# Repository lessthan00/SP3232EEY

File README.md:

# SP3232EEY

[SP3232EEY](https://www.jlc-smt.com/lcsc/detail?componentCode=C13482)

RS232芯片

[参考](https://oshwhub.com/jixin/TTL_RS232_SP3232EBEN_TR-14223d79138e415bb89689d060db1c6d)

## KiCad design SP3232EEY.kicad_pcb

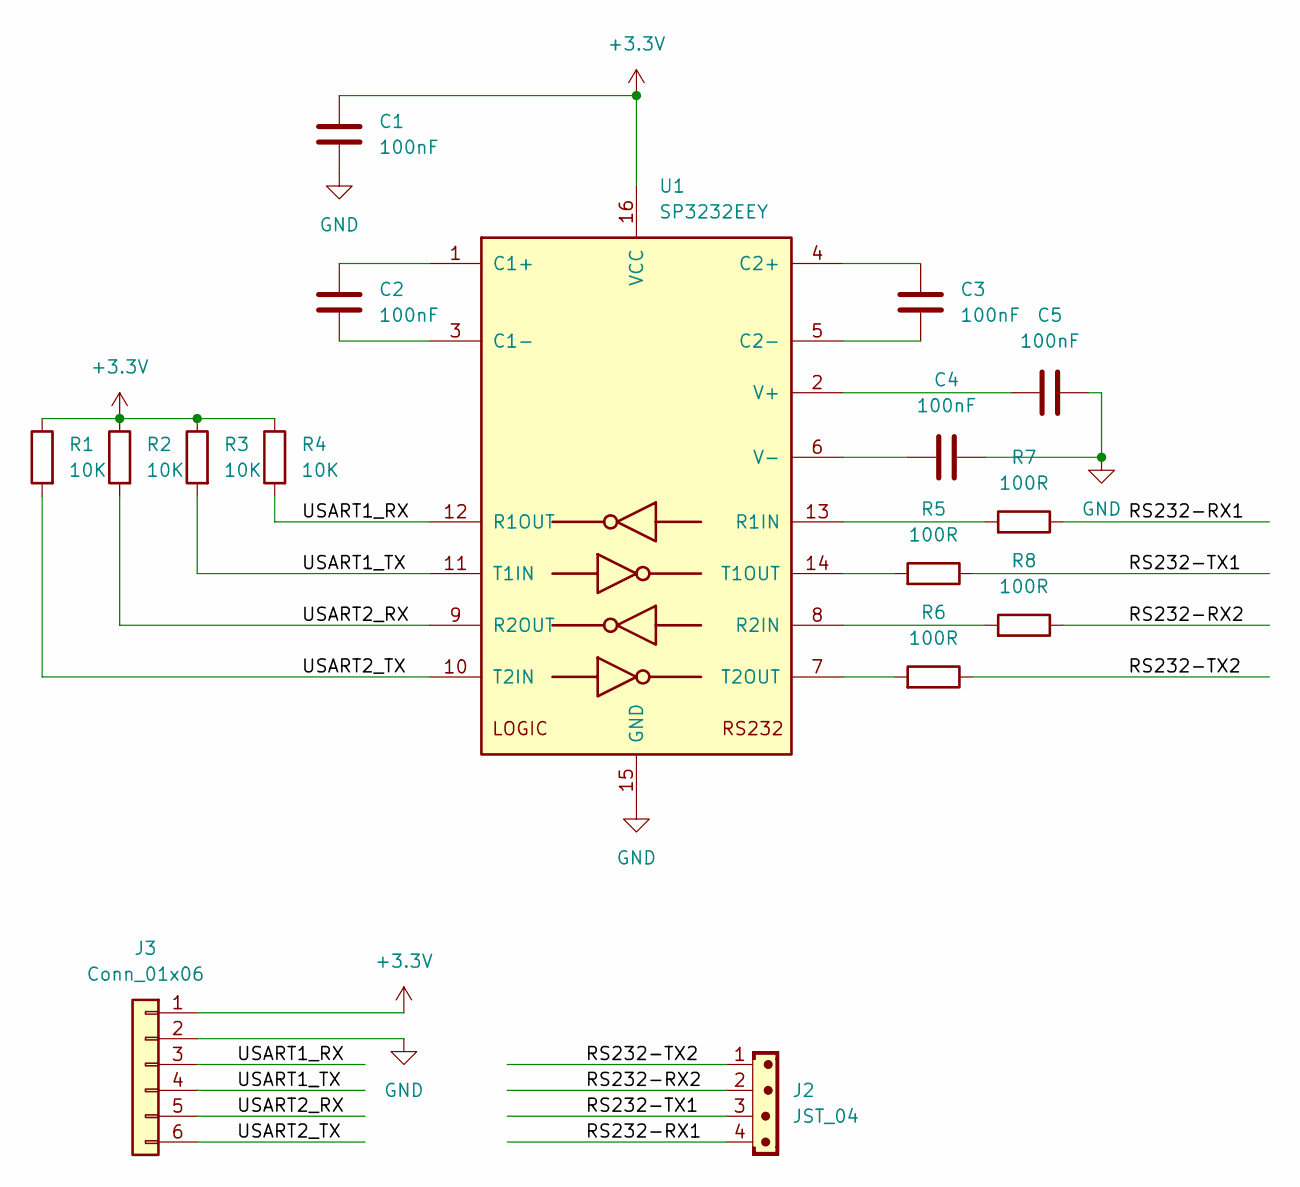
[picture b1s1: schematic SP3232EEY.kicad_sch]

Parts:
C1, C2, C3, C4, C5: 100nF; C_1206_3216Metric
J2: JST_04; TerminalBlock_Phoenix_MKDS-1,5-4-5.08_1x04_P5.08mm_Horizont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
J3: Conn_01x06; PinHeader_1x06_P2.54mm_Vertical
R1, R2, R3, R4: 10K; R_1206_3216Metric
R5, R6, R7, R8: 100R; R_1206_3216Metric
U1: SP3232EEY; SSOP-16_5.3x6.2mm_P0.65mm

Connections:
+3.3V: C1.2, J3.1, R1.2, R2.2, R3.2, R4.2, U1.16 (VCC)
/RS232-RX1: J2.4, R7.2
/RS232-RX2: J2.2, R8.2
/RS232-TX1: J2.3, R5.2
/RS232-TX2: J2.1, R6.2
/USART1_RX: J3.3, R4.1, U1.12 (R1OUT)
/USART1_TX: J3.4, R3.1, U1.11 (T1IN)
/USART2_RX: J3.5, R2.1, U1.9 (R2OUT)
/USART2_TX: J3.6, R1.1, U1.10 (T2IN)
GND: C1.1, C4.1, C5.1, J3.2, U1.15 (GND)
unnamed: C2.2, U1.1 (C1+)
unnamed: C2.1, U1.3 (C1-)
unnamed: C3.2, U1.4 (C2+)
unnamed: C3.1, U1.5 (C2-)
unnamed: R7.1, U1.13 (R1IN)
unnamed: R8.1, U1.8 (R2IN)
unnamed: R5.1, U1.14 (T1OUT)
unnamed: R6.1, U1.7 (T2OUT)
unnamed: C5.2, U1.2 (V+)
unnamed: C4.2, U1.6 (V-)

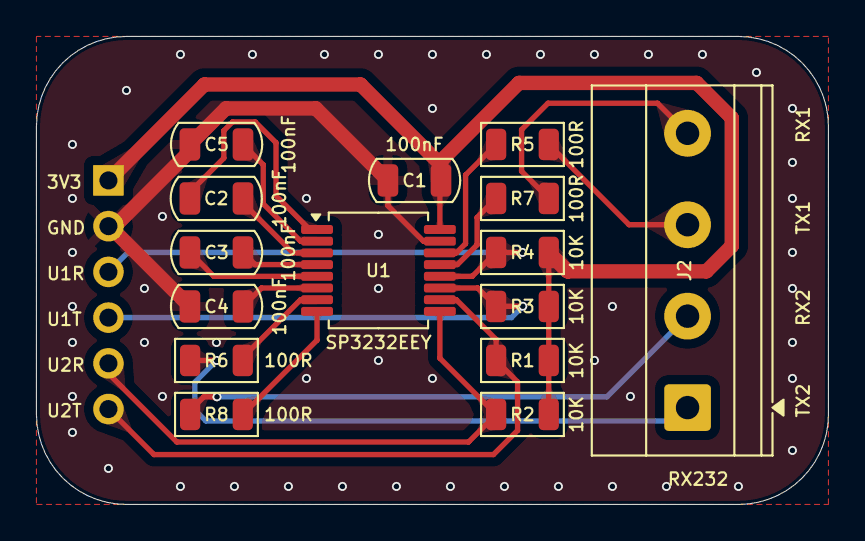
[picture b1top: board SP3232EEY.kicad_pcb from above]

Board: 2 copper layers, 44.0 x 26.0 mm, 16 parts (1 on the bottom side), 20 nets.
